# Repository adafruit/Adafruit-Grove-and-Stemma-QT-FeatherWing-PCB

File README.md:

## Adafruit Grove and Stemma QT FeatherWing for all Feathers PCB

<a href="http://www.adafruit.com/products/5862"><br/>
Click here to purchase one from the Adafruit shop</a>

PCB files for the Adafruit Grove and Stemma QT FeatherWing for all Feathers. 

Format is EagleCAD schematic and board layout
* https://www.adafruit.com/product/5862

### Description

The Adafruit Grove and Stemma QT FeatherWing for all Feathers allows folks to use many Grove devices with Feather boards! It fits nicely on top and has 3x Analog/Digital connectors, 1x UART connector and 2x I2C connectors. Not a ton, but enough to get many small projects going! We even managed to fit a vertical Stemma QT port on the end for another I2C connection.

Grove is a plug-and-play system from Seeed that features a 4-pin 2mm pitch connector (that is not JST PH). One thing to note is that the same connector is used for analog, digital, I2C, PWM, or UART: power, ground and two signals. So before plugging in a Grove sensor please make sure that you have the right 'matching' port: UART Groves should only go into UART port. I2C Groves go only into the I2C ports. Also, not every Feather has 6 Analog inputs, for example the RP2040 Feathers have only 4, or have hardware UART that's available for peripheirals, like the ESP8266 - so be aware of the underlying Feather boards' capabilites!

Comes with an assembled FeatherWing and two pieces of 16-pin header. Some light soldering is required to attach the header so it can be plugged into your Feather or doubler.

### License

Adafruit invests time and resources providing this open source design, please support Adafruit and open-source hardware by purchasing products from [Adafruit](https://www.adafruit.com)!

Designed by Limor Fried/Ladyada for Adafruit Industries.

Creative Commons Attribution/Share-Alike, all text above must be included in any redistribution. 
See license.txt for additional details.

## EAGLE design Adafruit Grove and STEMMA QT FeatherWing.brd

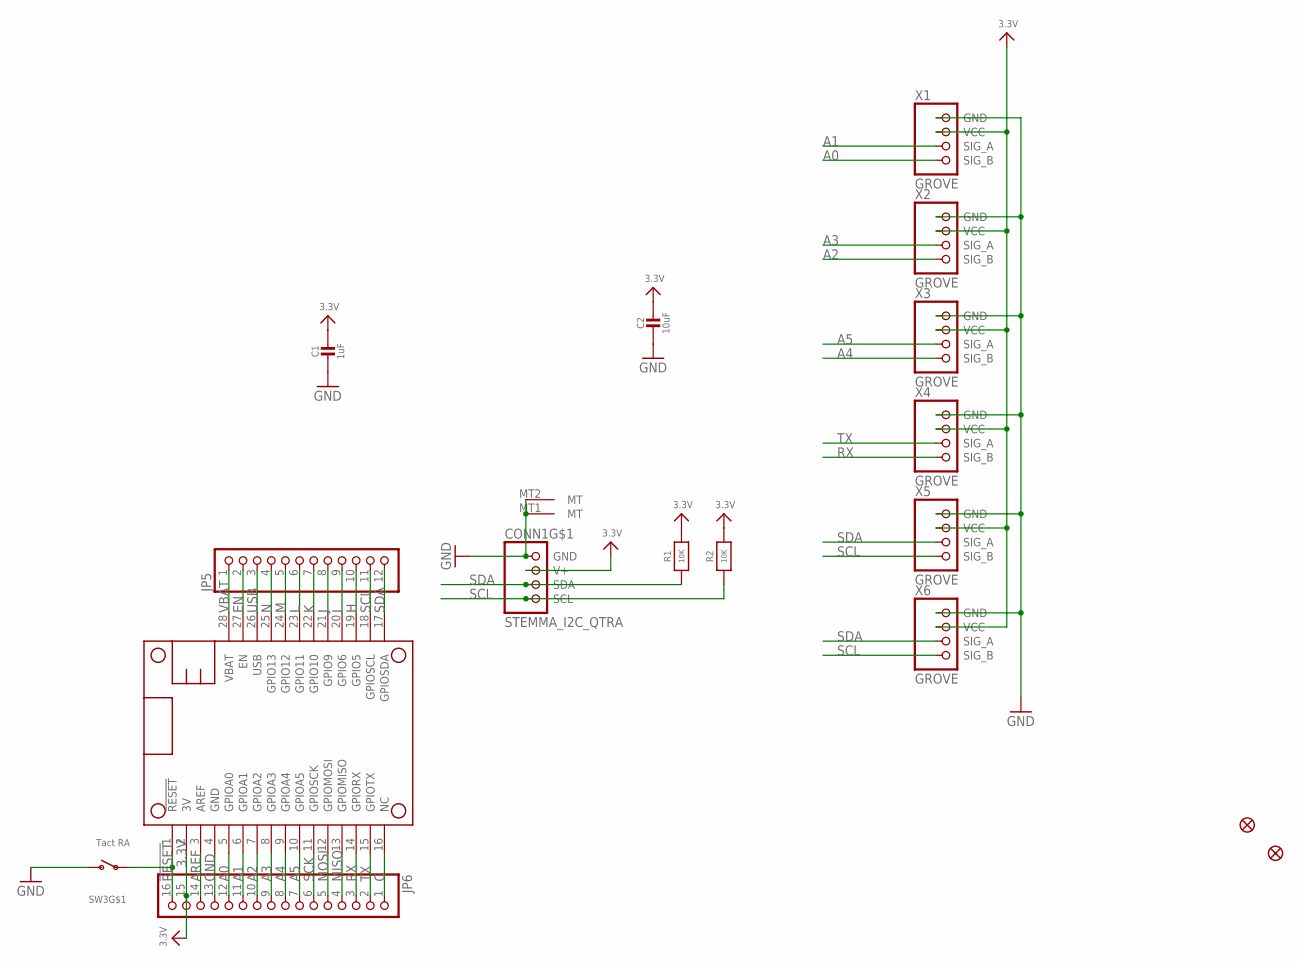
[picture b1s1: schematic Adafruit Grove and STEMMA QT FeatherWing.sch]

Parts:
C1: 1uF; 0603-NO
C2: 10uF; 0805-NO
CONN1: STEMMA_I2C_QTRA; JST_SH4_RA
FID1, FID2: FIDUCIAL_1MM
JP5: HEADER-1X12; 1X12_ROUND
JP6: HEADER-1X16ROUND; 1X16_ROUND
MS1: FEATHERWING_NODIM
R1, R2: 10K; 0603-NO
SW3: Tact RA; SPST_TACTILE_RA
X1, X2, X3, X4, X5, X6: GROVE; GROVE_SMTV

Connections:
3.3V: C1.1, C2.1, CONN1.2 (V+), JP6.15, MS1.2 (3V), R1.2, R2.2, X1.2 (VCC), X2.2 (VCC), X3.2 (VCC), X4.2 (VCC), X5.2 (VCC), X6.2 (VCC)
!RESET: JP6.16, MS1.1 (!RESET), SW3.1
A0: JP6.12, MS1.5 (GPIOA0), X1.4 (SIG_B)
A1: JP6.11, MS1.6 (GPIOA1), X1.3 (SIG_A)
A2: JP6.10, MS1.7 (GPIOA2), X2.4 (SIG_B)
A3: JP6.9, MS1.8 (GPIOA3), X2.3 (SIG_A)
A4: JP6.8, MS1.9 (GPIOA4), X3.4 (SIG_B)
A5: JP6.7, MS1.10 (GPIOA5), X3.3 (SIG_A)
AREF: JP6.14, MS1.3 (AREF)
EN: JP5.2, MS1.27 (EN)
G: JP6.1, MS1.16 (NC)
GND: C1.2, C2.2, CONN1.1 (GND), CONN1.MT1 (MT), CONN1.MT2 (MT), JP6.13, MS1.4 (GND), SW3.2 (S), X1.1 (GND), X1.MT1 (GND), X1.MT2 (GND), X2.1 (GND), X2.MT1 (GND), X2.MT2 (GND), X3.1 (GND), X3.MT1 (GND), X3.MT2 (GND), X4.1 (GND), X4.MT1 (GND), X4.MT2 (GND), X5.1 (GND), X5.MT1 (GND), X5.MT2 (GND), X6.1 (GND), X6.MT1 (GND), X6.MT2 (GND)
H: JP5.10, MS1.19 (GPIO5)
I: JP5.9, MS1.20 (GPIO6)
J: JP5.8, MS1.21 (GPIO9)
K: JP5.7, MS1.22 (GPIO10)
L: JP5.6, MS1.23 (GPIO11)
M: JP5.5, MS1.24 (GPIO12)
MISO: JP6.4, MS1.13 (GPIOMISO)
MOSI: JP6.5, MS1.12 (GPIOMOSI)
N: JP5.4, MS1.25 (GPIO13)
RX: JP6.3, MS1.14 (GPIORX), X4.4 (SIG_B)
SCK: JP6.6, MS1.11 (GPIOSCK)
SCL: CONN1.4 (SCL), JP5.11, MS1.18 (GPIOSCL), R2.1, X5.4 (SIG_B), X6.4 (SIG_B)
SDA: CONN1.3 (SDA), JP5.12, MS1.17 (GPIOSDA), R1.1, X5.3 (SIG_A), X6.3 (SIG_A)
TX: JP6.2, MS1.15 (GPIOTX), X4.3 (SIG_A)
USB: JP5.3, MS1.26 (USB)
VBAT: JP5.1, MS1.28 (VBAT)

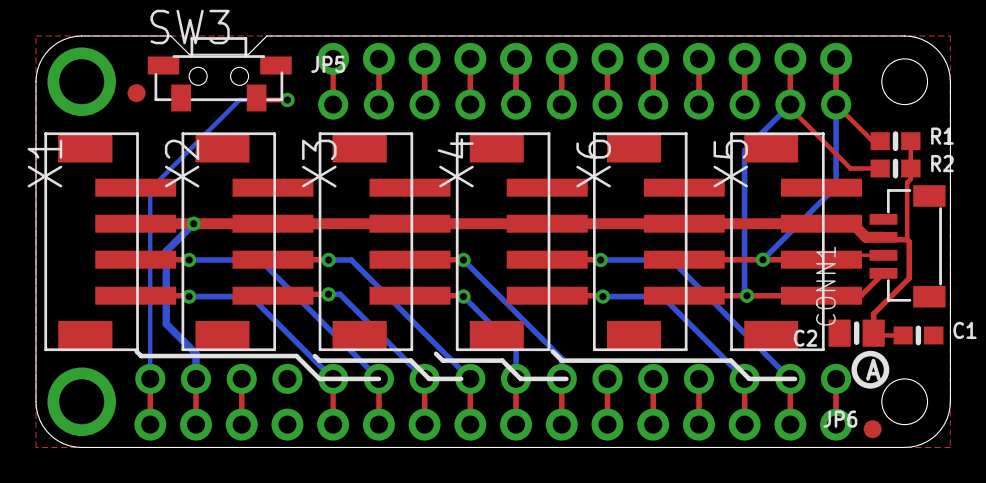
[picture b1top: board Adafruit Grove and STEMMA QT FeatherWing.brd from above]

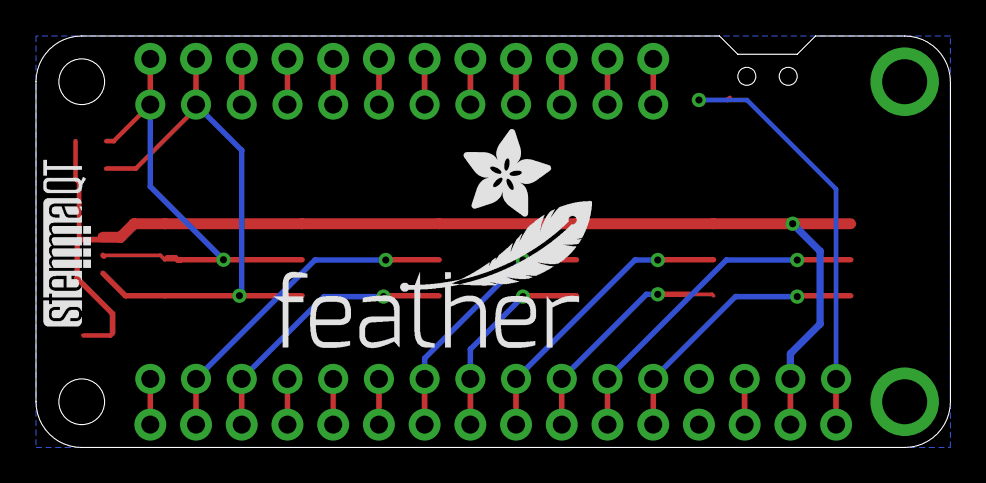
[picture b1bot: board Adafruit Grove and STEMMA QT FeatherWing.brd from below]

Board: 2 copper layers, 50.8 x 22.9 mm, 41 parts (5 on the bottom side), 28 nets.

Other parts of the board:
PLABEL0: PLABEL0
PLABEL1: PLABEL1
PLABEL2: PLABEL2
PLABEL3: PLABEL3
PLABEL4: PLABEL4
PLABEL5: PLABEL5
PLABEL6: PLABEL6
PLABEL7: PLABEL7
PLABEL8: PLABEL8
PLABEL9: PLABEL9
PLABEL10: PLABEL10
PLABEL11: PLABEL11
PLABEL12: PLABEL12
PLABEL13: PLABEL13
PLABEL14: PLABEL14
PLABEL15: PLABEL15
PLABEL16: PLABEL16
PLABEL17: PLABEL17
PLABEL18: PLABEL18
PLABEL19: PLABEL19
U$5: FEATHERLOGO_MED
U$7: ADAFRUIT_5MM
U$8: PCBFEAT-REV-040
U$11: STEMMAQT

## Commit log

2023-12-21 cookiecutter

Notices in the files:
parts and their libraries:
microbuilder: This work is placed in the public domain, and may be freely used for commercial and non-commercial work with the following conditions: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
